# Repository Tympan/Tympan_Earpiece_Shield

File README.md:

# Tympan_Earpiece_Shield
Shield for Tympan Rev D that supports Tympan BTE Hardware

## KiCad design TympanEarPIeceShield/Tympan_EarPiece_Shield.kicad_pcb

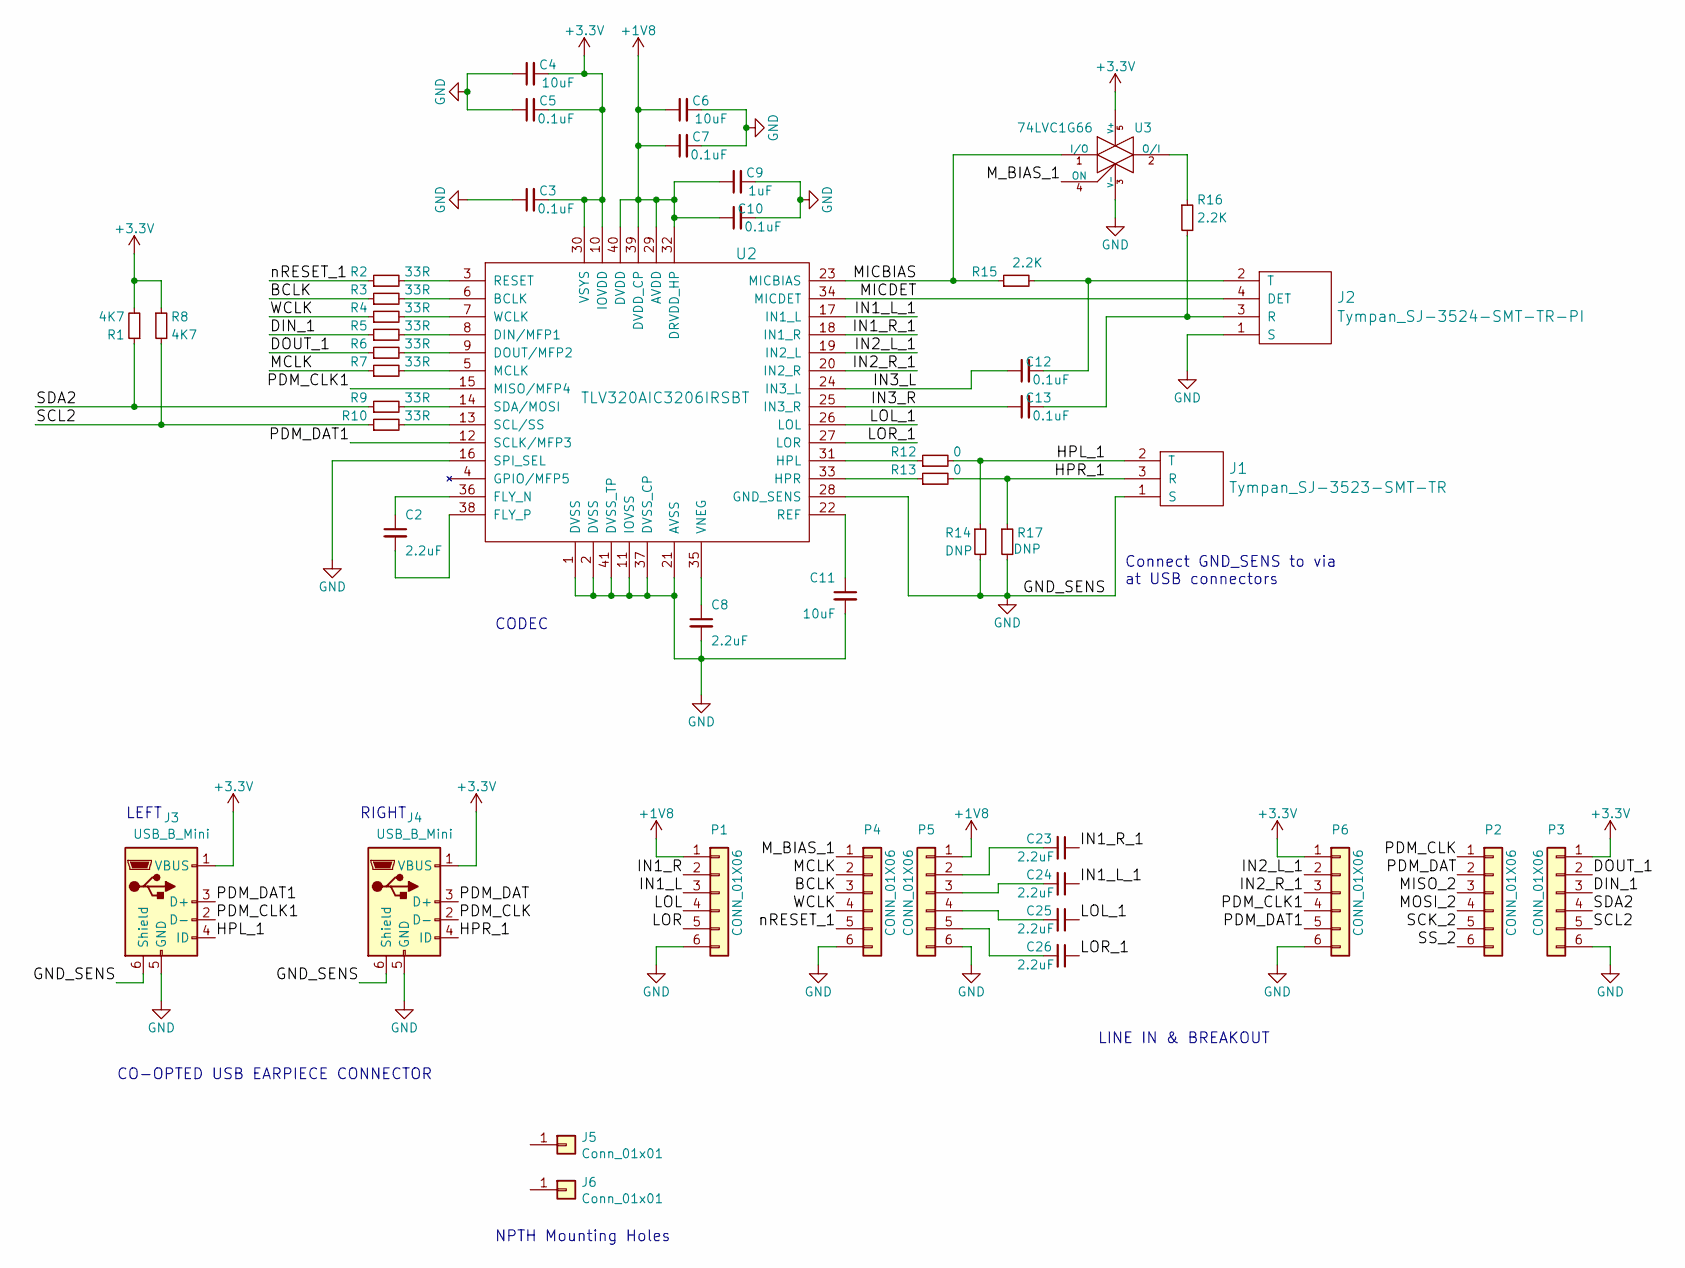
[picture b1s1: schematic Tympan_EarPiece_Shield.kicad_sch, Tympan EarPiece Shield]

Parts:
C2, C8, C23, C24, C25, C26: 2.2uF; C_0402
C3, C5, C7, C10, C12, C13: 0.1uF; C_0402
C4, C6, C11: 10uF; C_0402
C9: 1uF; C_0402
J1: Tympan_SJ-3523-SMT-TR; SJ-3523-SMT-TR
J2: Tympan_SJ-3524-SMT-TR-PI; SJ-3524-SMT-TR
J3, J4: USB_B_Mini; USB_MINI_MOLEX_51387-0578
J5, J6: Conn_01x01; MountingHole_3.2mm_M3
P1, P2, P3, P4, P5, P6: CONN_01X06; Pin_Header_Straight_1x06_Pitch2.54mm
R1, R8: 4K7; R_0402
R2, R3, R4, R5, R6, R7, R9, R10: 33R; R_0402
R12, R13: 0; C_0603
R14, R17: DNP; C_0603
R15, R16: 2.2K; C_0603
U2: TLV320AIC3206IRSBT; UQFN-40-1EP_5x5mm_Pitch0.4mm
U3: 74LVC1G66; SOT-353_SC-70-5

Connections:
+1V8: C6.1, C7.1, C9.1, C10.1, P1.1, P5.1, U2.29 (AVDD), U2.32 (DRVDD_HP), U2.39 (DVDD_CP), U2.40 (DVDD)
+3V3: C3.2, C4.2, C5.2, J3.1 (VBUS), J4.1 (VBUS), P3.1, P6.1, R1.2, R8.1, U2.10 (IOVDD), U2.30 (VSYS), U3.5 (V+)
/BCLK: P4.3, R3.1
/DIN_1: P3.3, R5.1
/DOUT_1: P3.2, R6.1
/HPL_1: J1.2 (T), J3.4 (ID), R12.2, R14.1
/HPR_1: J1.3 (R), J4.4 (ID), R13.2, R17.1
/IN1_L: P1.3
/IN1_L_1: C24.1, U2.17 (IN1_L)
/IN1_R: P1.2
/IN1_R_1: C23.1, U2.18 (IN1_R)
/IN2_L_1: P6.2, U2.19 (IN2_L)
/IN2_R_1: P6.3, U2.20 (IN2_R)
/IN3_L: C12.1, U2.24 (IN3_L)
/IN3_R: C13.1, U2.25 (IN3_R)
/LOL: P1.4
/LOL_1: C25.1, U2.26 (LOL)
/LOR: P1.5
/LOR_1: C26.1, U2.27 (LOR)
/MCLK: P4.2, R7.1
/MICBIAS: R15.1, U2.23 (MICBIAS), U3.1 (I/O)
/MICDET: J2.4 (DET), U2.34 (MICDET)
/MISO_2: P2.3
/MOSI_2: P2.4
/M_BIAS_1: P4.1, U3.4 (ON)
/PDM_CLK: J4.3 (D+), P2.2
/PDM_CLK1: J3.3 (D+), P6.5, U2.12 (SCLK/MFP3)
/PDM_DAT: J4.2 (D-), P2.1
/PDM_DAT1: J3.2 (D-), P6.4, U2.15 (MISO/MFP4)
/SCK_2: P2.5
/SCL2: P3.5, R8.2, R10.1
/SDA2: P3.4, R1.1, R9.1
/SS_2: P2.6
/WCLK: P4.4, R4.1
/nRESET_1: P4.5, R2.1
GND: C3.1, C4.1, C5.1, C6.2, C7.2, C8.2, C9.2, C10.2, C11.2, J1.1 (S), J2.1 (S), J3.5 (GND), J3.6 (Shield), J4.5 (GND), J4.6 (Shield), P1.6, P3.6, P4.6, P5.6, P6.6, R14.2, R17.2, U2.1 (DVSS), U2.2 (DVSS), U2.11 (IOVSS), U2.16 (SPI_SEL), U2.21 (AVSS), U2.28 (GND_SENS), U2.37 (DVSS_CP), U2.41 (DVSS_TP), U3.3 (V-)
unnamed: C2.1, U2.36 (FLY_N)
unnamed: C2.2, U2.38 (FLY_P)
unnamed: C8.1, U2.35 (VNEG)
unnamed: C11.1, U2.22 (REF)
unnamed: C12.2, J2.2 (T), R15.2
unnamed: C13.2, J2.3 (R), R16.2
unnamed: C23.2, P5.2
unnamed: C24.2, P5.3
unnamed: C25.2, P5.4
unnamed: C26.2, P5.5
unnamed: R2.2, U2.3 (RESET)
unnamed: R3.2, U2.6 (BCLK)
unnamed: R4.2, U2.7 (WCLK)
unnamed: R5.2, U2.8 (DIN/MFP1)
unnamed: R6.2, U2.9 (DOUT/MFP2)
unnamed: R7.2, U2.5 (MCLK)
unnamed: R9.2, U2.14 (SDA/MOSI)
unnamed: R10.2, U2.13 (SCL/SS)
unnamed: R12.1, U2.31 (HPL)
unnamed: R13.1, U2.33 (HPR)
unnamed: R16.1, U3.2 (O/I)

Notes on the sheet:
CO-OPTED USB EARPIECE CONNECTOR
LEFT
NPTH Mounting Holes
Connect GND_SENS to via at USB connectors
RIGHT
CODEC
LINE IN & BREAKOUT

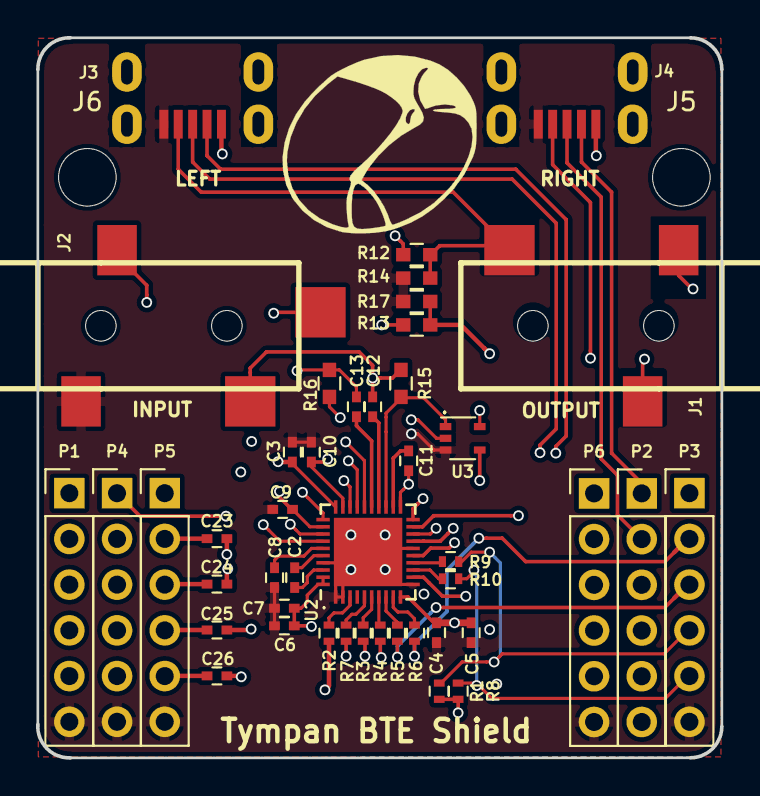
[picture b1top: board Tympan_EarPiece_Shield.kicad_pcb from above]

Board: 4 copper layers, 38.0 x 40.0 mm, 46 parts (0 on the bottom side), 49 nets.

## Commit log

2019-10-30 Initial Commit!
2019-11-19 Added mounting holes
2019-11-19 Adjusted top copper pour. Updated top image
2019-12-01 Added pdf from prototype fab house
2020-02-21 Removed spaaces in file names
2020-03-26 Fixed file names that were breaking things
2020-03-26 commited first draft of Earpiece Enclosure STEP files
2020-04-01 Added edrawing of entire enclosure assembly
2020-04-01 added STLs
2020-12-09 Moved bad silk reference out of the way
2021-06-24 Create BOM_TYMPAN_EARPIECE_SHIELD_ENCLOSURE.xlsx
    Added hardware for belt clip that was missing
2021-07-07 Tidy silk
2021-07-12 Silk and audio jack positioning
2025-09-17 Fixed bug in PDM CLK and DAT lines
    CLK and DAT circuits were swapped.
    Swapping them back in all components fixes this bug and does not require any re-routing. This addresses #4
